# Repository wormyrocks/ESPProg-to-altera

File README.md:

# ESP-Prog to Altera adapter

Lets you use a $10 [ESP-Prog](https://docs.espressif.com/projects/esp-iot-solution/en/latest/hw-reference/ESP-Prog_guide.html) programmer as the equivalent of an Altera USB Blaster.  

The FT2232HL on the ESP-Prog supports JTAG/MPSSE, which means you can use it to flash an FPGA using [openFPGALoader](https://trabucayre.github.io/openFPGALoader/compatibility/cable.html).  

This board can be ordered assembled from JLCPCB using the gerbers and BOM included in the release/ directory. Or you can hand solder it, obviously.  

# Update

It works. Tested with [Waveshare CoreEP4CE6](https://www.waveshare.com/wiki/CoreEP4CE6).

`openFPGALoader -c ft2232 --fpga-part ep4ce622 -f [binary].rbf`

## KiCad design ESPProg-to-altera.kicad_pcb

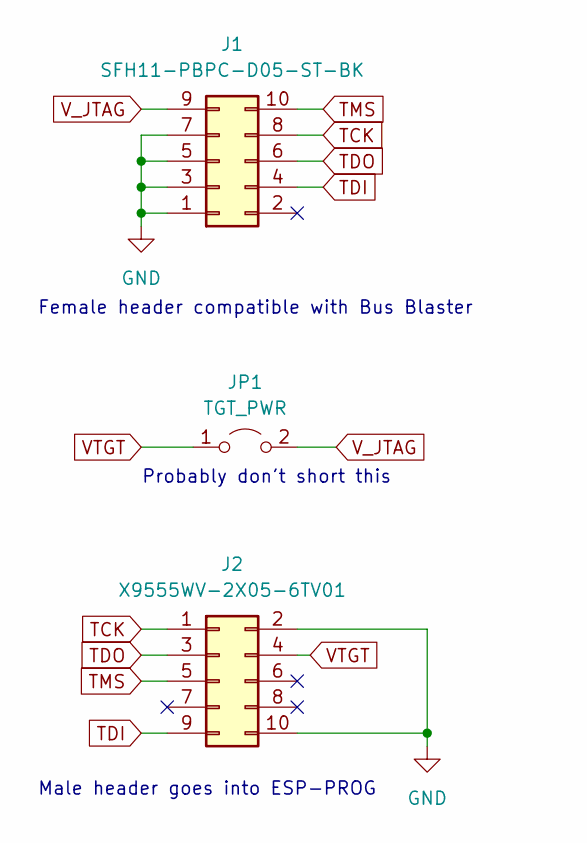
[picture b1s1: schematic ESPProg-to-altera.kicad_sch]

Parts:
J1: SFH11-PBPC-D05-ST-BK; IDC-Header_2x05_P2.54mm_Vertical; LCSC C3322462
J2: X9555WV-2X05-6TV01; IDC-Header_2x05_P2.54mm_Vertical; LCSC C706914
JP1: TGT_PWR; SolderJumper-2_P1.3mm_Open_TrianglePad1.0x1.5mm

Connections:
GND: J1.1, J1.3, J1.5, J1.7, J2.2, J2.10
TCK: J1.8, J2.1
TDI: J1.4, J2.9
TDO: J1.6, J2.3
TMS: J1.10, J2.5
VTGT: J2.4, JP1.1 (A)
V_JTAG: J1.9, JP1.2 (B)

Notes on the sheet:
Male header goes into ESP-PROG
Probably don't short this
Female header compatible with Bus Blaster

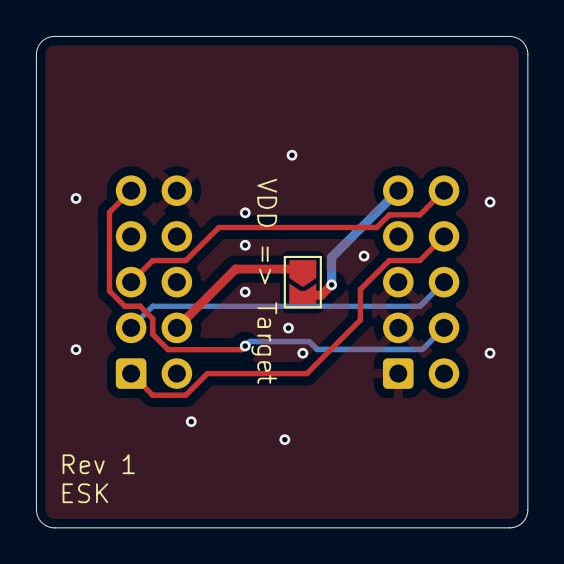
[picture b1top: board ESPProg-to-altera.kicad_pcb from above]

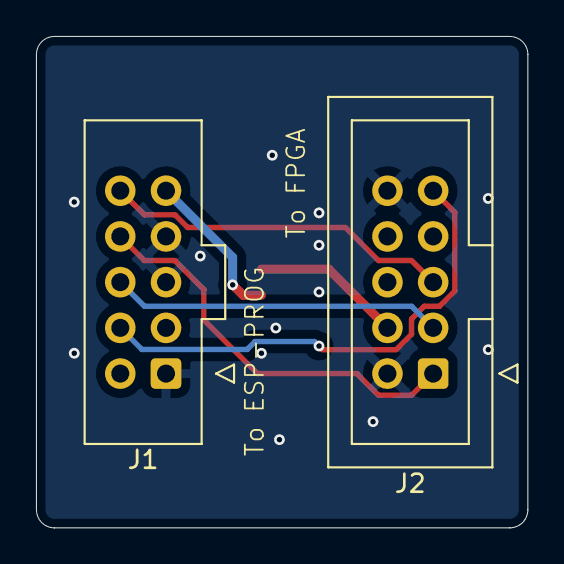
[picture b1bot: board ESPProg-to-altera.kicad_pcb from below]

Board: 2 copper layers, 27.3 x 27.3 mm, 3 parts (2 on the bottom side), 7 nets.
